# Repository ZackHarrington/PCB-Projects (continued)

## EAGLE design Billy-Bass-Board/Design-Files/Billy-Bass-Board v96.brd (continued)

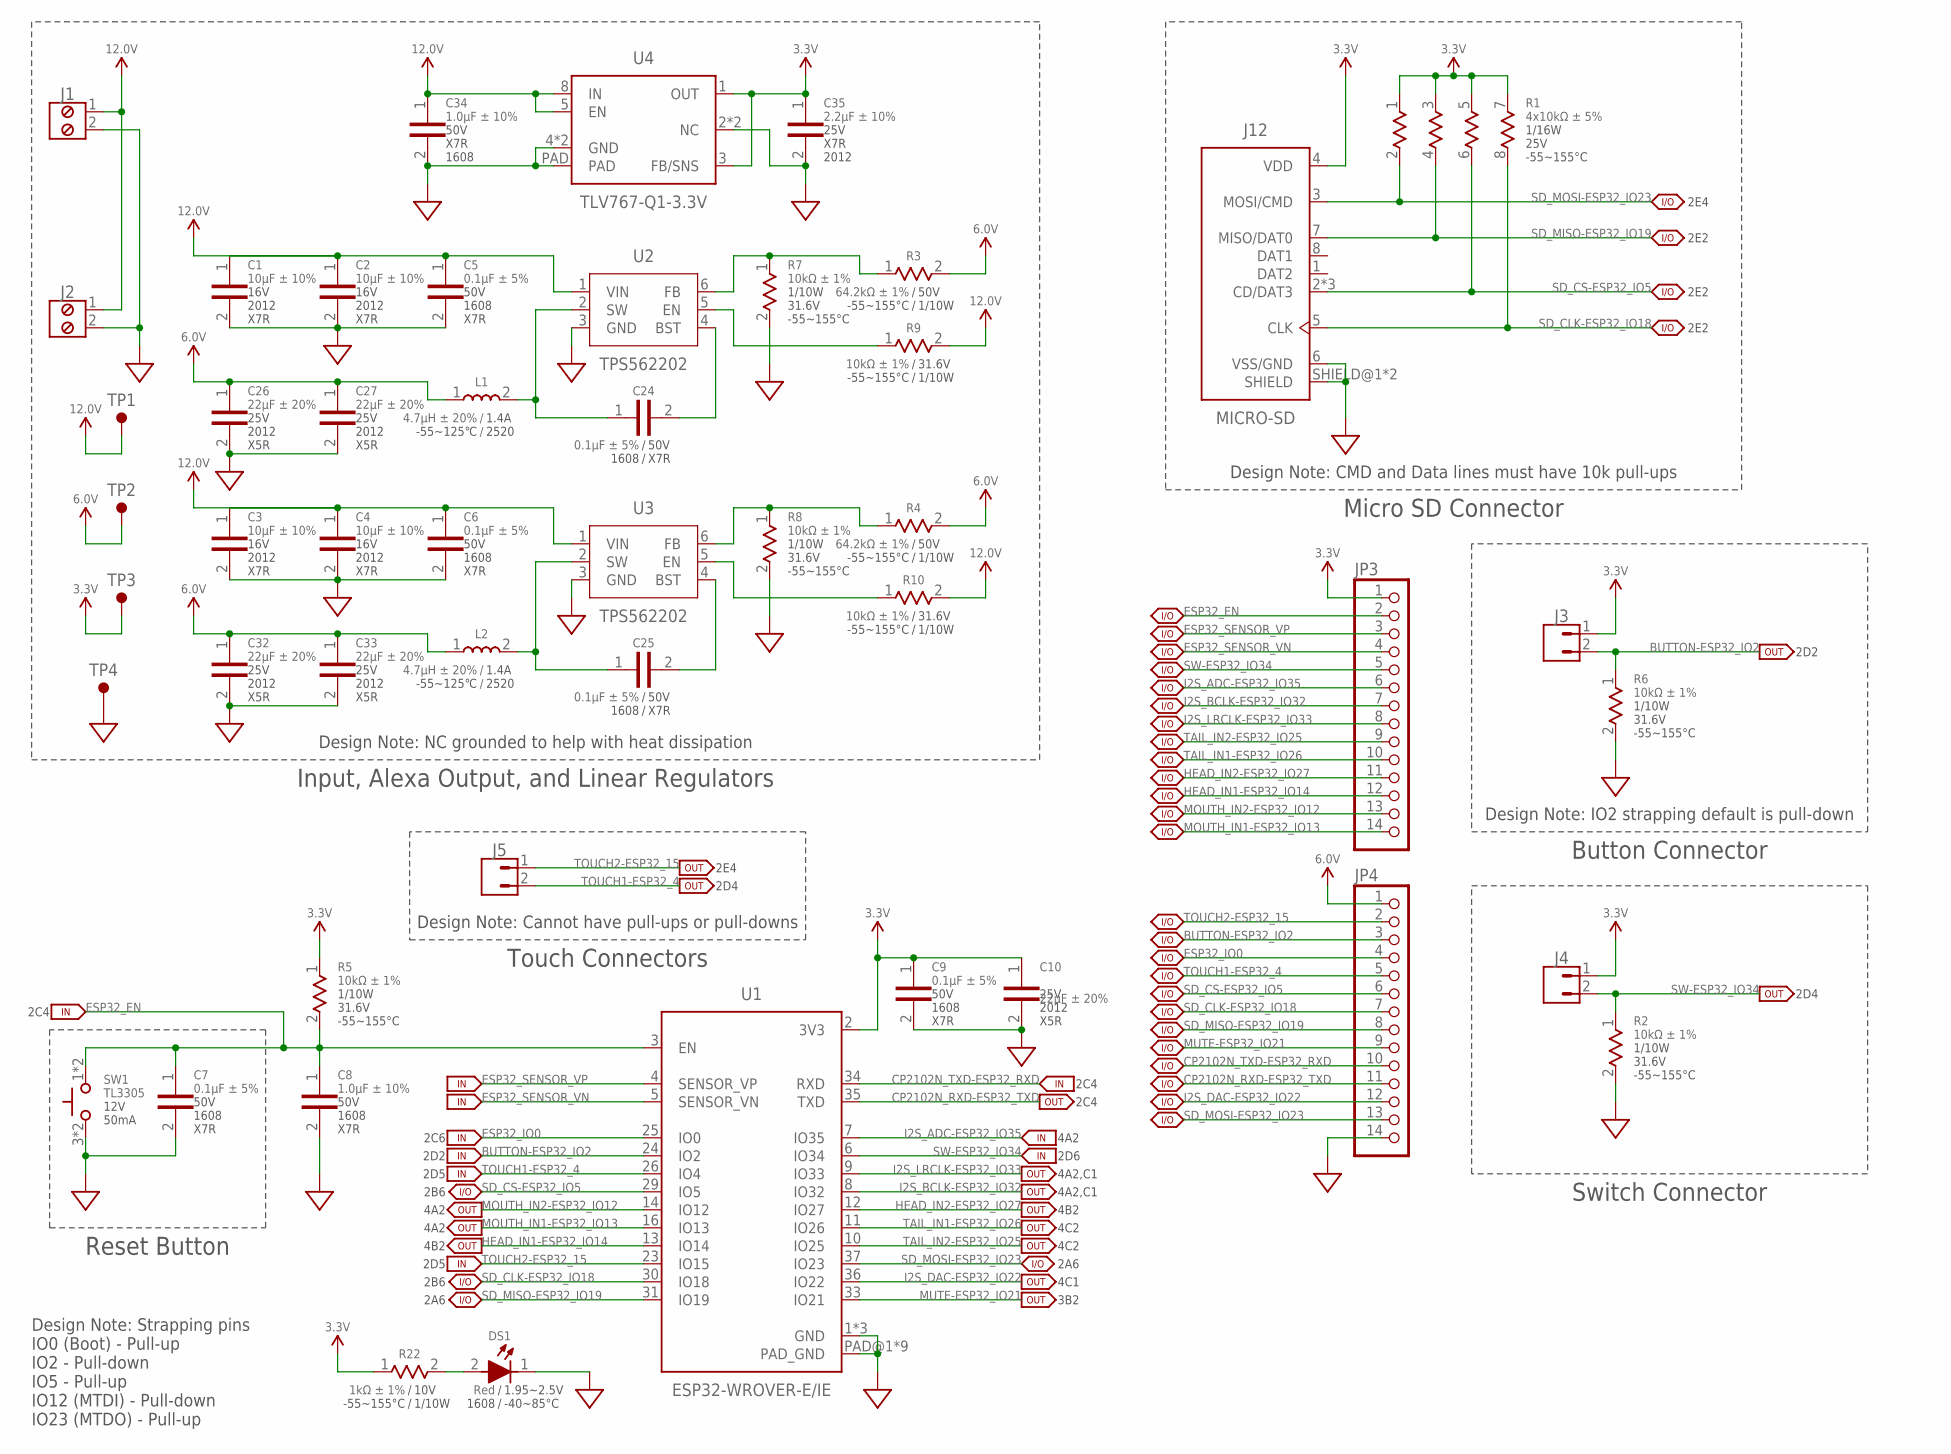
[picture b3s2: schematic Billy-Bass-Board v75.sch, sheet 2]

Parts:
C1, C2, C3, C4: 10µF ± 10%; 2012-SEM
C5, C6, C7, C9, C24, C25: 0.1µF ± 5%; 1608-SEM
C8, C34: 1.0µF ± 10%; 1608-SEM
C10, C26, C27, C32, C33: 22µF ± 20%; 2012-SEM
C35: 2.2µF ± 10%; 2012-SEM
DS1: Red; 1608
J1, J2: MPT-2-SCREW; MPT-0.5/2-2.54
J3, J4, J5: JST-XH-2; B2B-XH-A
J12: MICRO-SD; MEM2061
JP3, JP4: PINHD-1X14; 1X14
L1, L2: 4.7µH ± 20%; 2520-SEM
R1: 4x10kΩ ± 5%; 2010-4P-SEM
R2, R5, R6, R7, R8, R9, R10: 10kΩ ± 1%; 1608-SEM
R3, R4: 64.2kΩ ± 1%; 1608-SEM
R22: 1kΩ ± 1%; 1608-SEM
SW1: TL3305
TP1, TP2, TP3, TP4: TEST-POINT
U1: ESP32-WROVER-E/IE
U2, U3: TPS562202; SOT563
U4: TLV767-Q1-3.3V; VSON

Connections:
3.3V: C9.1, C10.1, C35.1, J3.1, J4.1, J12.4 (VDD), JP3.1, R1.1, R1.3, R1.5, R1.7, R5.1, R22.1, TP3.TP, U1.2 (3V3), U4.1 (OUT), U4.3 (FB/SNS); also elsewhere on the board
6.0V: C26.1, C27.1, C32.1, C33.1, JP4.1, L1.1, L2.1, R3.2, R4.2, TP2.TP; also elsewhere on the board
12.0V: C1.1, C2.1, C3.1, C4.1, C5.1, C6.1, C34.1, J1.1, J2.1, R9.2, R10.2, TP1.TP, U2.1 (VIN), U3.1 (VIN), U4.5 (EN), U4.8 (IN)
BUTTON-ESP32_IO2: J3.2, JP4.3, R6.1, U1.24 (IO2)
CP2102N_RXD-ESP32_TXD: JP4.11, U1.35 (TXD)
CP2102N_TXD-ESP32_RXD: JP4.10, U1.34 (RXD)
ESP32_EN: C7.1, C8.1, JP3.2, R5.2, SW1.1 (2), SW1.2, U1.3 (EN)
ESP32_IO0: JP4.4, U1.25 (IO0)
ESP32_SENSOR_VN: JP3.4, U1.5 (SENSOR_VN)
ESP32_SENSOR_VP: JP3.3, U1.4 (SENSOR_VP)
GND: C1.2, C2.2, C3.2, C4.2, C5.2, C6.2, C7.2, C8.2, C9.2, C10.2, C26.2, C27.2, C32.2, C33.2, C34.2, C35.2, DS1.1, J1.2, J2.2, J12.6 (VSS/GND), J12.SHIELD@1 (SHIELD), J12.SHIELD@2 (SHIELD), JP4.14, R2.2, R6.2, R7.2, R8.2, SW1.3 (1), SW1.4 (1), TP4.TP, U1.1 (GND), U1.15 (GND), U1.38 (GND), U1.PAD@1 (PAD_GND), U1.PAD@2 (PAD_GND), U1.PAD@3 (PAD_GND), U1.PAD@4 (PAD_GND), U1.PAD@5 (PAD_GND), U1.PAD@6 (PAD_GND), U1.PAD@7 (PAD_GND), U1.PAD@8 (PAD_GND), U1.PAD@9 (PAD_GND), U2.3 (GND), U3.3 (GND), U4.2 (NC), U4.4 (GND), U4.6 (GND), U4.7 (NC), U4.PAD; also elsewhere on the board
HEAD_IN1-ESP32_IO14: JP3.12, U1.13 (IO14); also elsewhere on the board
HEAD_IN2-ESP32_IO27: JP3.11, U1.12 (IO27); also elsewhere on the board
I2S_ADC-ESP32_IO35: JP3.6, U1.7 (IO35); also elsewhere on the board
I2S_BCLK-ESP32_IO32: JP3.7, U1.8 (IO32); also elsewhere on the board
I2S_DAC-ESP32_IO22: JP4.12, U1.36 (IO22); also elsewhere on the board
I2S_LRCLK-ESP32_IO33: JP3.8, U1.9 (IO33); also elsewhere on the board
MOUTH_IN1-ESP32_IO13: JP3.14, U1.16 (IO13); also elsewhere on the board
MOUTH_IN2-ESP32_IO12: JP3.13, U1.14 (IO12); also elsewhere on the board
MUTE-ESP32_IO21: JP4.9, U1.33 (IO21); also elsewhere on the board
unnamed: DS1.2, R22.2
SD_CLK-ESP32_IO18: J12.5 (CLK), JP4.7, R1.8, U1.30 (IO18)
SD_CS-ESP32_IO5: J12.2 (CD/DAT3), J12.CD@1 (CD/DAT3), J12.CD@2 (CD/DAT3), JP4.6, R1.6, U1.29 (IO5)
SD_MISO-ESP32_IO19: J12.7 (MISO/DAT0), JP4.8, R1.4, U1.31 (IO19)
SD_MOSI-ESP32_IO23: J12.3 (MOSI/CMD), JP4.13, R1.2, U1.37 (IO23)
SW-ESP32_IO34: J4.2, JP3.5, R2.1, U1.6 (IO34)
TAIL_IN1-ESP32_IO26: JP3.10, U1.11 (IO26); also elsewhere on the board
TAIL_IN2-ESP32_IO25: JP3.9, U1.10 (IO25); also elsewhere on the board
TOUCH1-ESP32_4: J5.2, JP4.5, U1.26 (IO4)
TOUCH2-ESP32_15: J5.1, JP4.2, U1.23 (IO15)
TPS5622021_BST: C24.2, U2.4 (BST)
TPS5622021_EN: R9.1, U2.5 (EN)
TPS5622021_FB: R3.1, R7.1, U2.6 (FB)
TPS5622021_SW: C24.1, L1.2, U2.2 (SW)
TPS5622022_BST: C25.2, U3.4 (BST)
TPS5622022_EN: R10.1, U3.5 (EN)
TPS5622022_FB: R4.1, R8.1, U3.6 (FB)
TPS5622022_SW: C25.1, L2.2, U3.2 (SW)

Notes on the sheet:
Input, Alexa Output, and Linear Regulators
Reset Button
2E4
2E2
Micro SD Connector
2D2
Button Connector
Design Note: IO2 strapping default is pull-down
2C4
2A6
2C6
2B6
Design Note: NC grounded to help with heat dissipation
Design Note: CMD and Data lines must have 10k pull-ups
Design Note: Strapping pins IO0 (Boot) - Pull-up IO2 - Pull-down IO5 - Pull-up IO12 (MTDI) - Pull-down IO23 (MTDO) - Pull-up
Design Note: Cannot have pull-ups or pull-downs
Touch Connectors
Switch Connector
4A2
4B2
4C2
2D4
2D5
2D6
4A2,C1
4C1
3B2

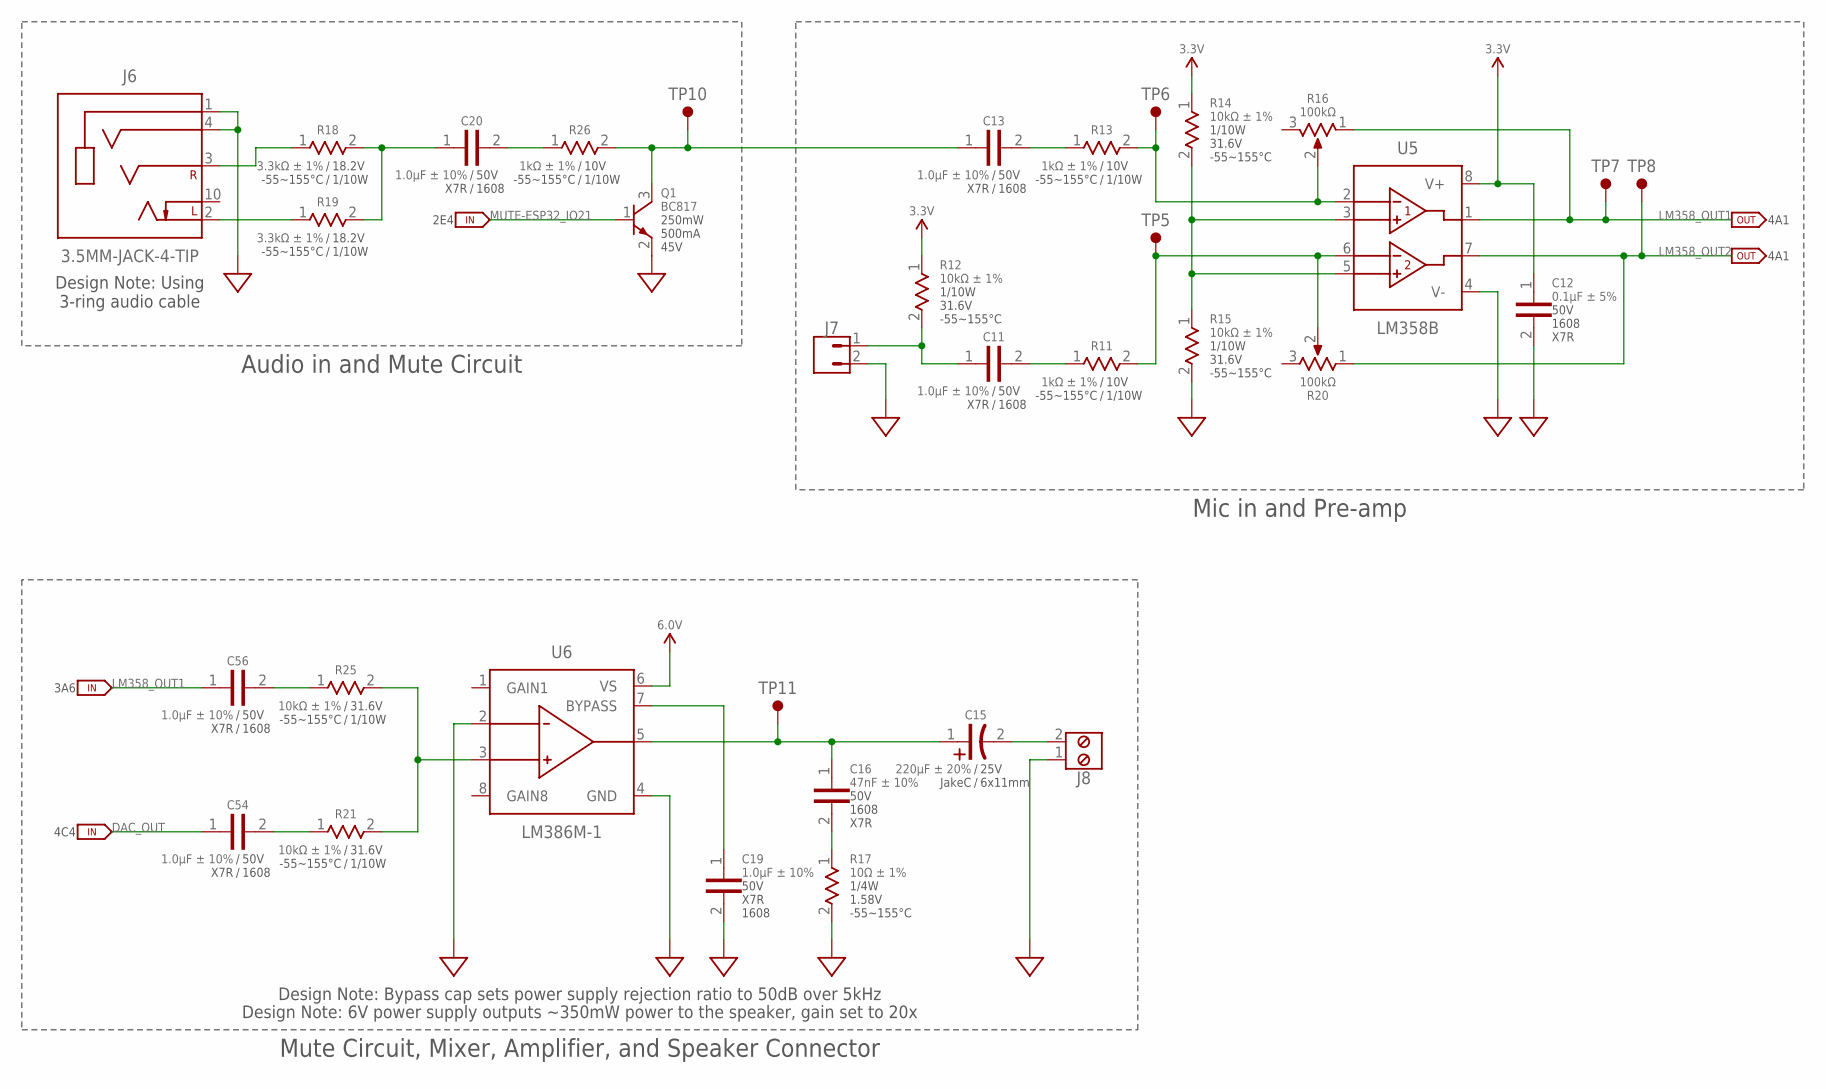
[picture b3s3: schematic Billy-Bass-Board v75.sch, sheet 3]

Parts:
C11, C13, C19, C20, C54, C56: 1.0µF ± 10%; 1608-SEM
C12: 0.1µF ± 5%; 1608-SEM
C15: 220µF ± 20%; 6X11-E-FLAT-REV
C16: 47nF ± 10%; 1608-SEM
J6: 3.5MM-JACK-4-TIP; SJ2-358940-SMT
J7: JST-XH-2; B2B-XH-A
J8: MPT-2-SCREW; MPT-0.5/2-2.54
Q1: BC817; SOT-23-3
R11, R13, R26: 1kΩ ± 1%; 1608-SEM
R12, R14, R15, R21, R25: 10kΩ ± 1%; 1608-SEM
R16, R20: 100kΩ; 3314J
R17: 10Ω ± 1%; 3216-SEM
R18, R19: 3.3kΩ ± 1%; 1608-SEM
TP5, TP6, TP7, TP8, TP10, TP11: TEST-POINT
U5: LM358B; D0008A-SOIC
U6: LM386M-1; D0008A-SOIC

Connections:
3.3V: C12.1, R12.1, R14.1, U5.8 (V+); also elsewhere on the board
6.0V: U6.6 (VS); also elsewhere on the board
AUX_LEFT: J6.2 (TIP), R19.1
AUX_MIXED: C20.1, R18.2, R19.2
AUX_MUTE: C13.1, Q1.3 (C), R26.2, TP10.TP
AUX_RIGHT: J6.3 (RING_1), R18.1
DAC_OUT: C54.1; also elsewhere on the board
GND: C12.2, C19.2, J6.1 (SLEEVE), J6.4 (RING_2), J7.2, J8.1, Q1.2 (E), R15.2, R17.2, U5.4 (V-), U6.2 (-INPUT), U6.4 (GND); also elsewhere on the board
LM358_IN1-: R13.2, R16.2, TP6.TP, U5.2 (IN1-)
LM358_IN2-: R11.2, R20.2, TP5.TP, U5.6 (IN2-)
LM358_IN+: R14.2, R15.1, U5.3 (IN1+), U5.5 (IN2+)
LM358_OUT1: C56.1, R16.1, TP7.TP, U5.1 (OUT1); also elsewhere on the board
LM358_OUT2: R20.1, TP8.TP, U5.7 (OUT2); also elsewhere on the board
LM386M_BYPASS: C19.1, U6.7 (BYPASS)
LM386M_IN+: R21.2, R25.2, U6.3 (+INPUT)
LM386M_OUT: C15.1, C16.1, TP11.TP, U6.5 (VOUT)
MIC+: C11.1, J7.1, R12.2
MUTE-ESP32_IO21: Q1.1 (B); also elsewhere on the board
unnamed: C54.2, R21.1
unnamed: C13.2, R13.1
unnamed: C20.2, R26.1
unnamed: C56.2, R25.1
unnamed: C11.2, R11.1
unnamed: C16.2, R17.1
SPEAKER+: C15.2, J8.2

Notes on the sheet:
Design Note: Using 3-ring audio cable
Mic in and Pre-amp
Mute Circuit, Mixer, Amplifier, and Speaker Connector
Design Note: 6V power supply outputs ~350mW power to the speaker, gain set to 20x
4A1
Design Note: Bypass cap sets power supply rejection ratio to 50dB over 5kHz
Audio in and Mute Circuit
2E4
4C4
3A6

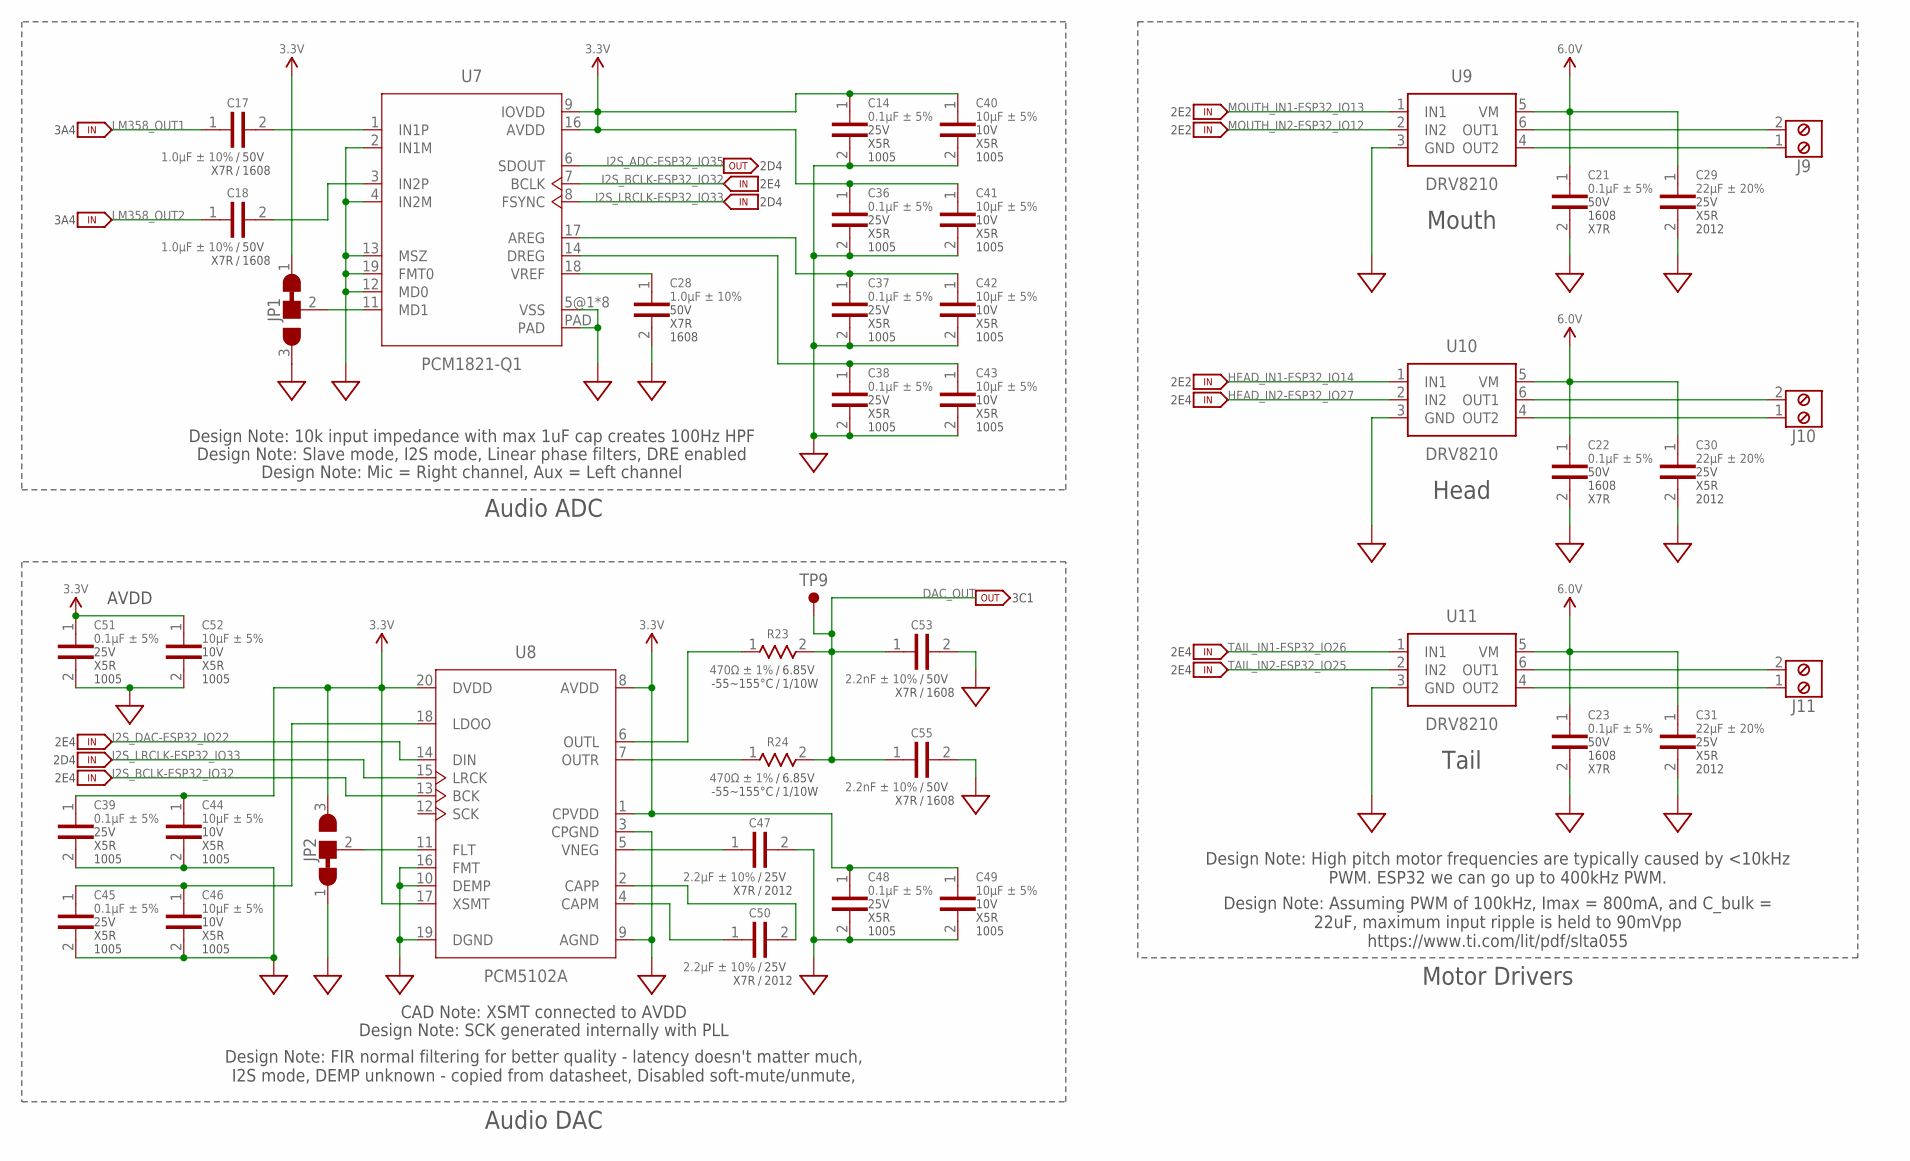
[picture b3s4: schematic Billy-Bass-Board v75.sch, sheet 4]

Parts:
C14, C36, C37, C38, C39, C45, C48, C51: 0.1µF ± 5%; 1005-SEM
C17, C18, C28: 1.0µF ± 10%; 1608-SEM
C21, C22, C23: 0.1µF ± 5%; 1608-SEM
C29, C30, C31: 22µF ± 20%; 2012-SEM
C40, C41, C42, C43, C44, C46, C49, C52: 10µF ± 5%; 1005-SEM
C47, C50: 2.2µF ± 10%; 2012-SEM
C53, C55: 2.2nF ± 10%; 1608-SEM
J9, J10, J11: MPT-2-SCREW; MPT-0.5/2-2.54
JP1, JP2: JUMPER-2-BRIDGED-1; JUMPER-PAD-2-BRIDGED-1
R23, R24: 470Ω ± 1%; 1608-SEM
TP9: TEST-POINT
U7: PCM1821-Q1; WQFN
U8: PCM5102A; TSSOP-20
U9, U10, U11: DRV8210; SOT563

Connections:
3.3V: C14.1, C36.1, C39.1, C40.1, C41.1, C44.1, C48.1, C49.1, C51.1, C52.1, JP1.1, JP2.3, U7.9 (IOVDD), U7.16 (AVDD), U8.1 (CPVDD), U8.8 (AVDD), U8.17 (XSMT), U8.20 (DVDD); also elsewhere on the board
6.0V: C21.1, C22.1, C23.1, C29.1, C30.1, C31.1, U9.5 (VM), U10.5 (VM), U11.5 (VM); also elsewhere on the board
DAC_OUT: C53.1, C55.1, R23.2, R24.2, TP9.TP; also elsewhere on the board
DRV82101_OUT1: J9.2, U9.6 (OUT1)
DRV82101_OUT2: J9.1, U9.4 (OUT2)
DRV82102_OUT1: J10.2, U10.6 (OUT1)
DRV82102_OUT2: J10.1, U10.4 (OUT2)
DRV82103_OUT1: J11.2, U11.6 (OUT1)
DRV82103_OUT2: J11.1, U11.4 (OUT2)
GND: C14.2, C21.2, C22.2, C23.2, C28.2, C29.2, C30.2, C31.2, C36.2, C37.2, C38.2, C39.2, C40.2, C41.2, C42.2, C43.2, C44.2, C45.2, C46.2, C47.2, C48.2, C49.2, C51.2, C52.2, C53.2, C55.2, JP1.3, JP2.1, U7.2 (IN1M), U7.4 (IN2M), U7.5@1 (VSS), U7.5@2 (VSS), U7.10@1 (VSS), U7.10@2 (VSS), U7.12 (MD0), U7.13 (MSZ), U7.15@1 (VSS), U7.15@2 (VSS), U7.19 (FMT0), U7.20@1 (VSS), U7.20@2 (VSS), U7.PAD, U8.3 (CPGND), U8.9 (AGND), U8.10 (DEMP), U8.16 (FMT), U8.19 (DGND), U9.3 (GND), U10.3 (GND), U11.3 (GND); also elsewhere on the board
HEAD_IN1-ESP32_IO14: U10.1 (IN1); also elsewhere on the board
HEAD_IN2-ESP32_IO27: U10.2 (IN2); also elsewhere on the board
I2S_ADC-ESP32_IO35: U7.6 (SDOUT); also elsewhere on the board
I2S_BCLK-ESP32_IO32: U7.7 (BCLK), U8.13 (BCK); also elsewhere on the board
I2S_DAC-ESP32_IO22: U8.14 (DIN); also elsewhere on the board
I2S_LRCLK-ESP32_IO33: U7.8 (FSYNC), U8.15 (LRCK); also elsewhere on the board
LM358_OUT1: C17.1; also elsewhere on the board
LM358_OUT2: C18.1; also elsewhere on the board
MOUTH_IN1-ESP32_IO13: U9.1 (IN1); also elsewhere on the board
MOUTH_IN2-ESP32_IO12: U9.2 (IN2); also elsewhere on the board
unnamed: JP1.2, U7.11 (MD1)
PCM1821_AREG: C37.1, C42.1, U7.17 (AREG)
PCM1821_DREG: C38.1, C43.1, U7.14 (DREG)
PCM1821_IN1P: C17.2, U7.1 (IN1P)
PCM1821_IN2P: C18.2, U7.3 (IN2P)
PCM1821_VREF: C28.1, U7.18 (VREF)
PCM5102A_CAPM: C50.1, U8.4 (CAPM)
PCM5102A_CAPP: C50.2, U8.2 (CAPP)
PCM5102A_FLT: JP2.2, U8.11 (FLT)
PCM5102A_LDOO: C45.1, C46.1, U8.18 (LDOO)
PCM5102A_OUTL: R23.1, U8.6 (OUTL)
PCM5102A_OUTR: R24.1, U8.7 (OUTR)
PCM5102A_VNEG: C47.1, U8.5 (VNEG)
TAIL_IN1-ESP32_IO26: U11.1 (IN1); also elsewhere on the board
TAIL_IN2-ESP32_IO25: U11.2 (IN2); also elsewhere on the board

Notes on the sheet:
Design Note: Assuming PWM of 100kHz, Imax = 800mA, and C_bulk = 22uF, maximum input ripple is held to 90mVpp https://www.ti.com/lit/pdf/slta055
Mouth
Head
Tail
2E2
2E4
Audio ADC
Design Note: Mic = Right channel, Aux = Left channel
Design Note: Slave mode, I2S mode, Linear phase filters, DRE enabled
Design Note: 10k input impedance with max 1uF cap creates 100Hz HPF
2D4
Motor Drivers
3A4
Design Note: High pitch motor frequencies are typically caused by <10kHz PWM. ESP32 we can go up to 400kHz PWM.
CAD Note: XSMT connected to AVDD
Design Note: FIR normal filtering for better quality - latency doesn't matter much, I2S mode, DEMP unknown - copied from datasheet, Disabled soft-mute/unmute,
Design Note: SCK generated internally with PLL
AVDD
Audio DAC
3C1

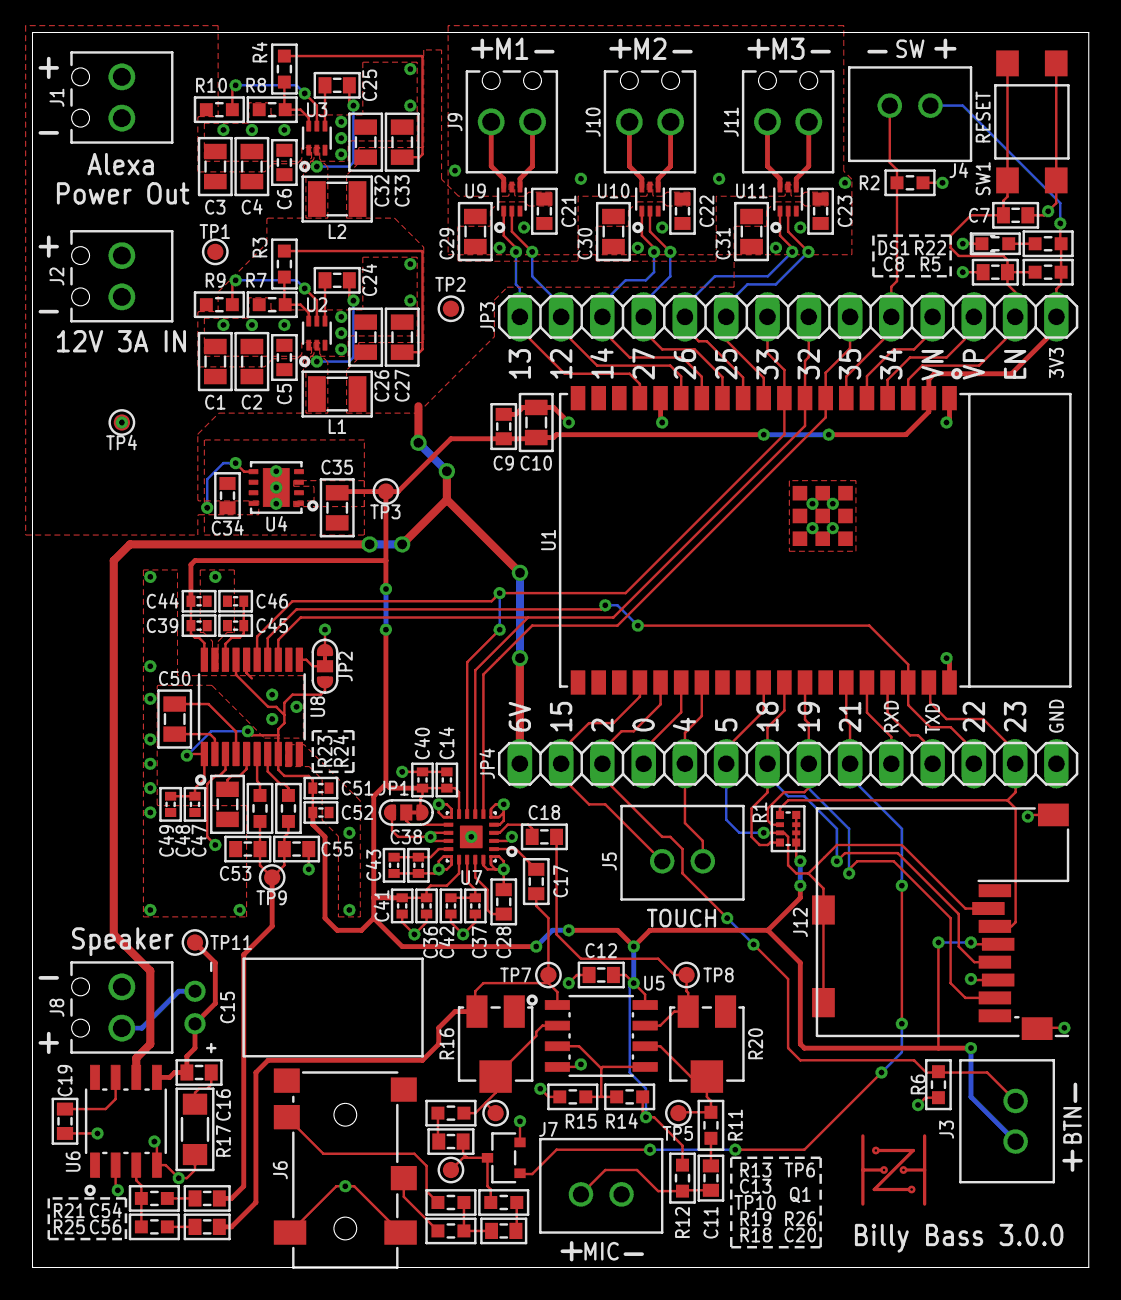
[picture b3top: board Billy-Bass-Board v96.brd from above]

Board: 2 copper layers, 65.0 x 76.0 mm, 126 parts (0 on the bottom side), 78 nets.

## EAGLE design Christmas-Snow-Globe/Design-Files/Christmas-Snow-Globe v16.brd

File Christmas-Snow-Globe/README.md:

# Christmas Snow Globe 

In this project, I combined my hobbies of PCB and electronics design, 3D modeling, 3D printing, and programming to create personalized snow globes for the holiday season. This README goes through the stages of development for this project and showcases the final build at the end.

## Introduction

I try to create personalized gifts for the holidays, and this year I set out to build something using lights and custom PCBs. After a brainstorming session with my roommate, I decided it would be really neat to incorporate personalized Lego minifigures of everyone. The only way of doing this that came to mind was building a snow globe around them. After plugging my thoughts into the Bing Image Generator and coming up with some concept drawings, I settled on keeping it simple with some timer-controlled LEDs and 3D printed casing. This way I could create a simple yet elegant design, while most importantly, having time to finish it. 

## Features

I initially decided on some key features for the snow globes, and then designed around them. These included:
- Custom Lego minifigures of each person or couple - which I ordered from pick-a-brick
- LED fairy lights to illuminate the minifigures and fit the holiday theme
- A 6-hour ON, 18-hour OFF timer for ease of use
- Battery powered - for ease of use and as a low power consumption challenge

## Design

After ordering the minifigure parts, I also ordered some cheap snow globe tops that would fit. For this I chose 2.7in (69mm) because everything else felt too big. The first part of the design entailed deciding on what batteries and electrical components to use, along with how they would all fit into the snow globe. Next, once I had a general PCB layout and model from Fusion360, I loaded it into Blender and created the snow globe stand parts. Lastly, I designed the fake snow the minifigures would stand on by modeling Lego piece connectors.

### 1. Electronic Design

The first challenge for the electronics design was how to build a precise 6-hour timer. I went through a few concepts such as a crystal oscillator and counter circuit but ultimately settled on using the cheap 8-bit ATtiny85 because it can be programmed with Arduino, is reliable within ~1 minute, and its power-down mode only draws 0.5uA. 

The next challenge was what batteries to use. I wanted them to be easy to find since I wouldn't be the one replacing them every year, but also to last the full month or two the snow globes were used. After considering size requirements and reading through other documentation, I settled on three AAA batteries. This gave me a voltage range of roughly 4.5 - 3.3V over the battery's life, satisfying the 2.6 - 2.7V requirement of the LED fairy lights and providing ample mAh for the expected 0.5 - 3mA draw (depending on the voltage over the LEDs). 

Lastly, I needed to keep the voltage over the LEDs steady for even brightness and low current consumption. During this time, I found a 2.7V linear regulator with very low quiescent current and decided to add a potentiometer in series with the LED fairy lights to allow for adjustable brightness and current consumption post production.

The final stage of the electronics design was to lay everything out on the PCB. To do this I marked out the snow globe dimensions and made sure to put everything in a good location while trying to make sure it was as simple as possible for everyone to access the batteries. The final render of this board can be seen below.

### 2. 3D Design

After I was set on the electronics and confident they would work, I began to create the stand for the snow globe which would also house the PCB and batteries. Because I originally planned on adding some organic detailing to the outside of the stand, I chose to model everything in Blender. I ultimately liked the simple look of the stand itself better, so it probably wasn't necessary, but since I had everything in Blender I decided to also use some of the displacement modifiers to create a snowy scene for the characters to stand on. Below is a render of the final 3D modeled pieces, unfortunately the minifigure textures didn't copy over when I imported them from a past project.

### 3. Programming

The last big challenge of this project, aside from getting everything in time, was to actually program the ATtiny85 to act as a 6-hour timer. This took a while to learn as I had never used interrupts or 8-bit microprocessors before, but ultimately didn't prove to be too difficult. I found configuring the watchdog as an interrupt gave me a pretty steady average of 8.955s per interrupt. This wasn't amazing in terms of accurately measuring 6 hours, but it was the most power efficient way of doing it. And at the end of the day, no one will notice that the timer originally set to turn on at 5:00 p.m. now turns on at 5:04 p.m. a month later.

## Construction

Here I have included some images of the physical construction of each part and the final product.

### Soldered Board

### Stand Top

### Stand Bottom

### Final Product

Update: After almost 2 months the device is still functional. The LED brightness has dimmed a bit, but they still turn on around roughly the same time indicating the timer and power draw calculations were accurate. 

## License

This is just a hobby creation I made as a gift so feel free to do whatever you want with this design if you happened upon it. However, I would recommend reading the considerations below and modifying it or building your own rather than copying it.

## Project Considerations

The following are some things I learned from this project for myself or anyone else to consider when doing something similar.
- I built the stand to screw into the plastic globes which causes the wire connecting the LED strips to the PCB to coil up and sometimes break. In the future, not screwing in the globes or allowing the PCB itself to rotate may be more reliable.
- The Lego pick-a-brick items took about a month and a half to arrive (I got them 3 days before Christmas) 
- There are more accurate and power conservative ways to create a timer, this was just simple and easy to adjust on the fly
- The AAA batteries worked great but they do slip around on the contacts, they should probably have physical dividers between them to hold them in place.

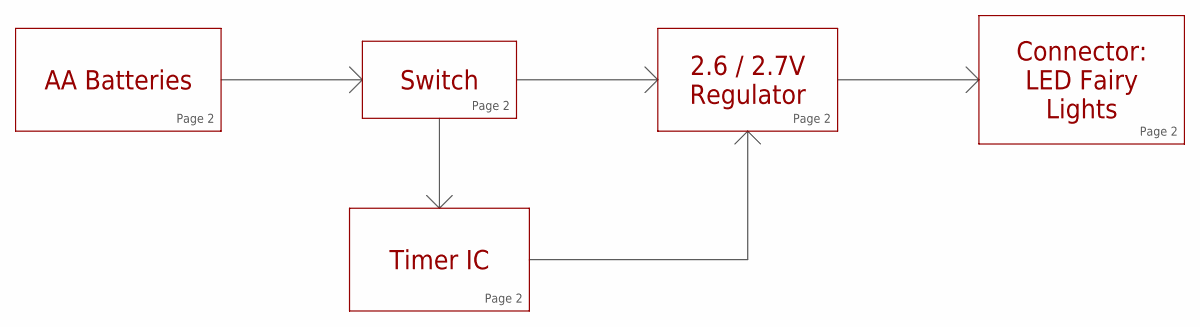
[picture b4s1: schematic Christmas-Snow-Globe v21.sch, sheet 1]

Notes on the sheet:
Switch
AA Batteries
Timer IC
Connector: LED Fairy Lights
2.6 / 2.7V Regulator
Page 2

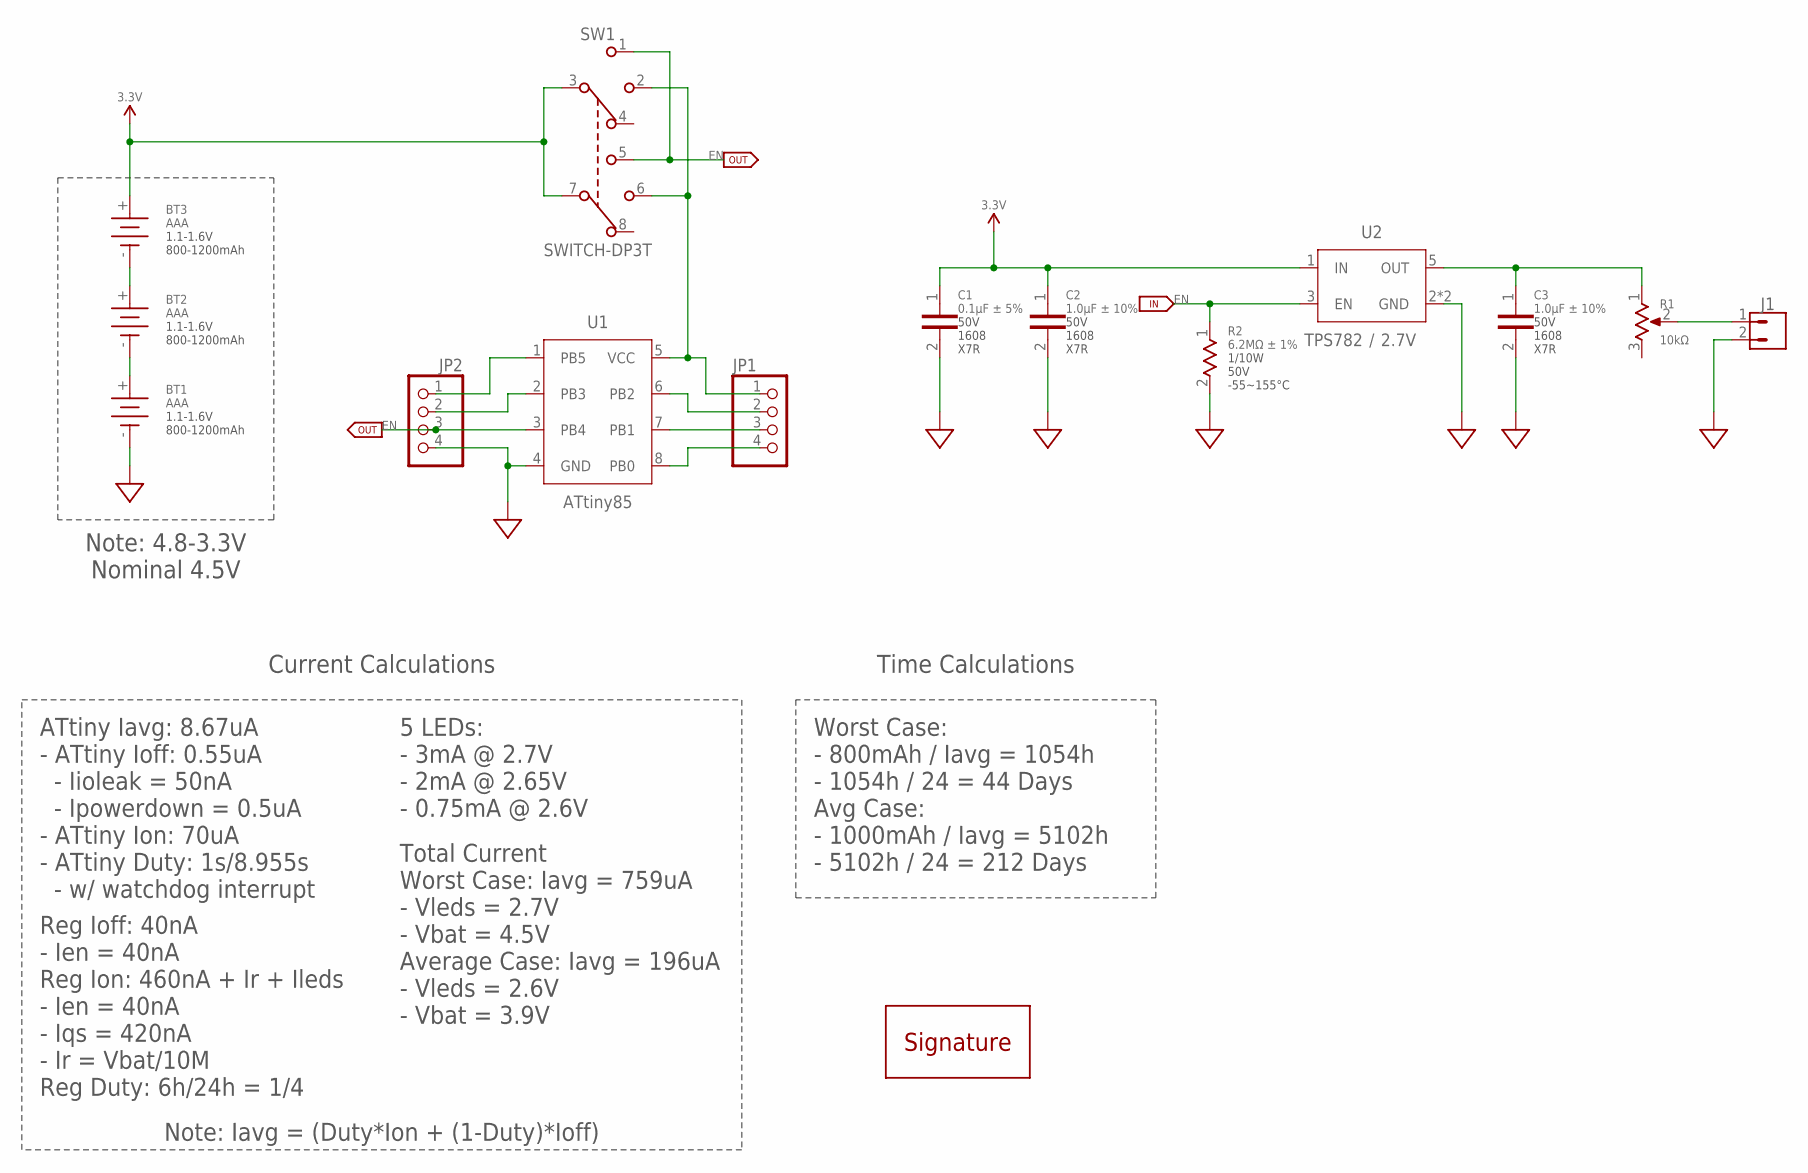
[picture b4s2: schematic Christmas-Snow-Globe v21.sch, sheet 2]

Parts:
BT1, BT2, BT3: AAA; AAA-CONTACTS
C1: 0.1µF ± 5%; 1608-SEM
C2, C3: 1.0µF ± 10%; 1608-SEM
J1: JST-PH-2; B2B-PH-K-S
JP1, JP2: PINHD-1X4; 1X04
R1: 10kΩ; 3314J
R2: 6.2MΩ ± 1%; 1608-SEM
SW1: SWITCH-DP3T; EG2301
U1: ATtiny85; 8P3-PDIP
U2: TPS782; SOT-23-5
U$14: SIGNATURE

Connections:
3.3V: BT3.+, C1.1, C2.1, SW1.3, SW1.7, U2.1 (IN)
EN: JP2.3, R2.1, SW1.1, SW1.5, U1.3 (PB4), U2.3 (EN)
GND: BT1.-, C1.2, C2.2, C3.2, J1.2, JP2.4, R2.2, U1.4 (GND), U2.2 (GND), U2.4 (GND)
LEDS+: J1.1, R1.2
unnamed: BT2.+, BT3.-
unnamed: BT1.+, BT2.-
PB0: JP1.4, U1.8 (PB0)
PB1: JP1.3, U1.7 (PB1)
PB2: JP1.2, U1.6 (PB2)
PB3: JP2.2, U1.2 (PB3)
PB5: JP2.1, U1.1 (PB5)
TIMER: JP1.1, SW1.2, SW1.6, U1.5 (VCC)
TPS782_OUT: C3.1, R1.1, U2.5 (OUT)

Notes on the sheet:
Note: 4.8-3.3V Nominal 4.5V
Current Calculations
ATtiny Iavg: 8.67uA - ATtiny Ioff: 0.55uA - Iioleak = 50nA - Ipowerdown = 0.5uA - ATtiny Ion: 70uA - ATtiny Duty: 1s/8.955s - w/ watchdog interrupt
5 LEDs: - 3mA @ 2.7V - 2mA @ 2.65V - 0.75mA @ 2.6V
Reg Ioff: 40nA - Ien = 40nA Reg Ion: 460nA + Ir + Ileds - Ien = 40nA - Iqs = 420nA - Ir = Vbat/10M Reg Duty: 6h/24h = 1/4
Total Current Worst Case: Iavg = 759uA - Vleds = 2.7V - Vbat = 4.5V Average Case: Iavg = 196uA - Vleds = 2.6V - Vbat = 3.9V
Note: Iavg = (Duty*Ion + (1-Duty)*Ioff)
Time Calculations
Worst Case: - 800mAh / Iavg = 1054h - 1054h / 24 = 44 Days Avg Case: - 1000mAh / Iavg = 5102h - 5102h / 24 = 212 Days

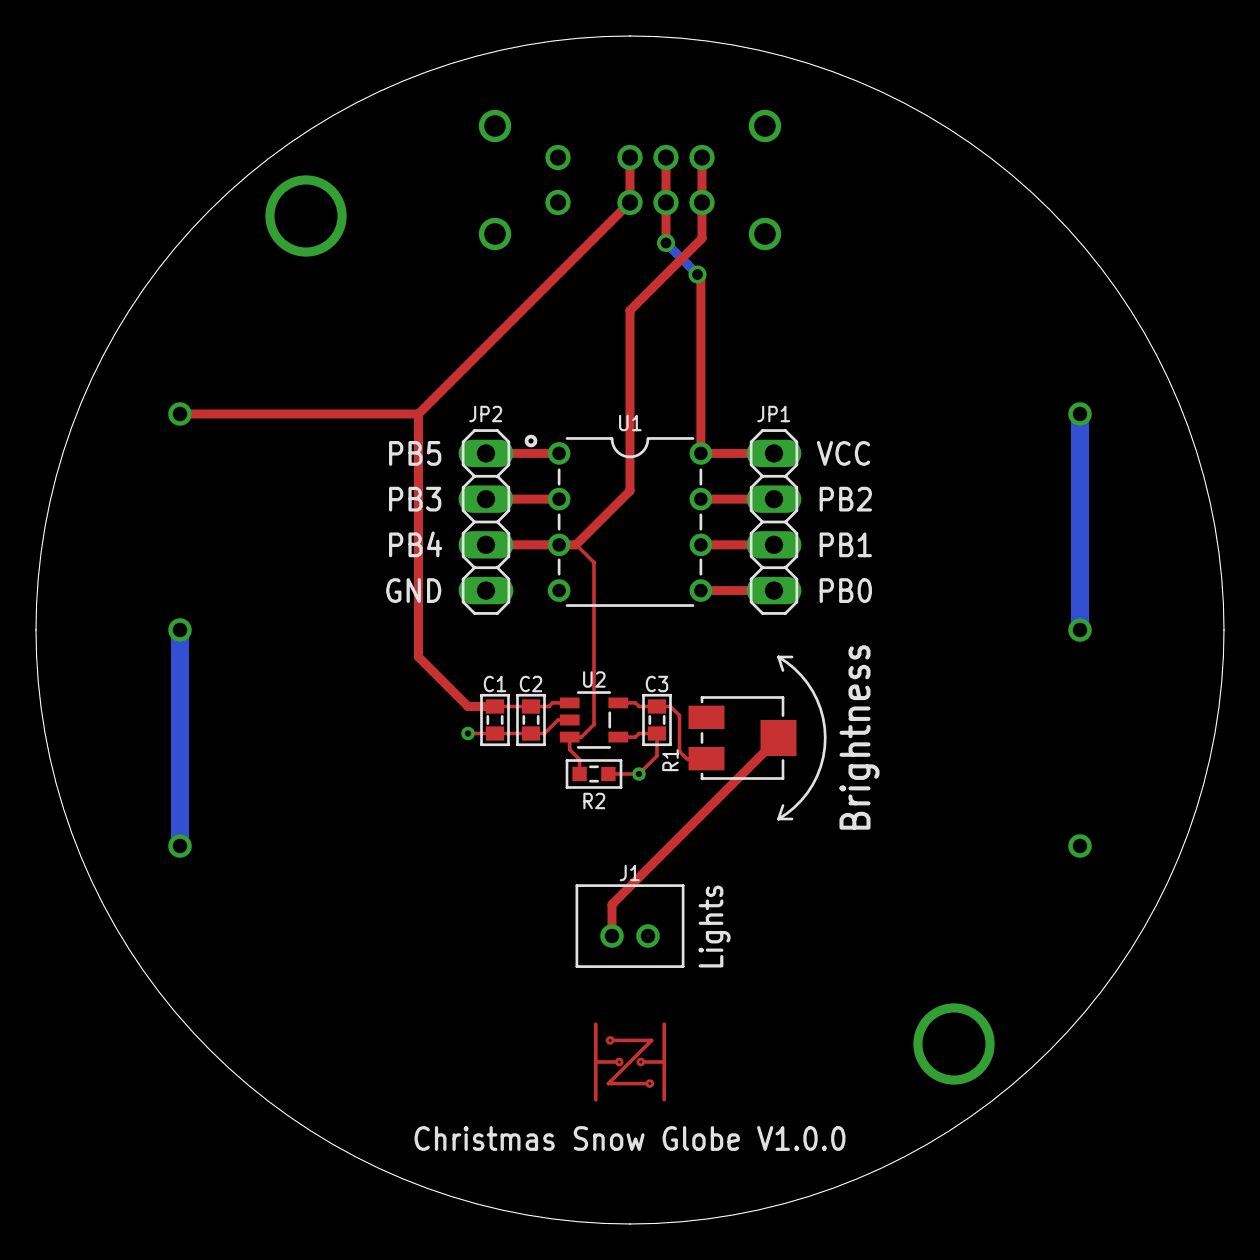
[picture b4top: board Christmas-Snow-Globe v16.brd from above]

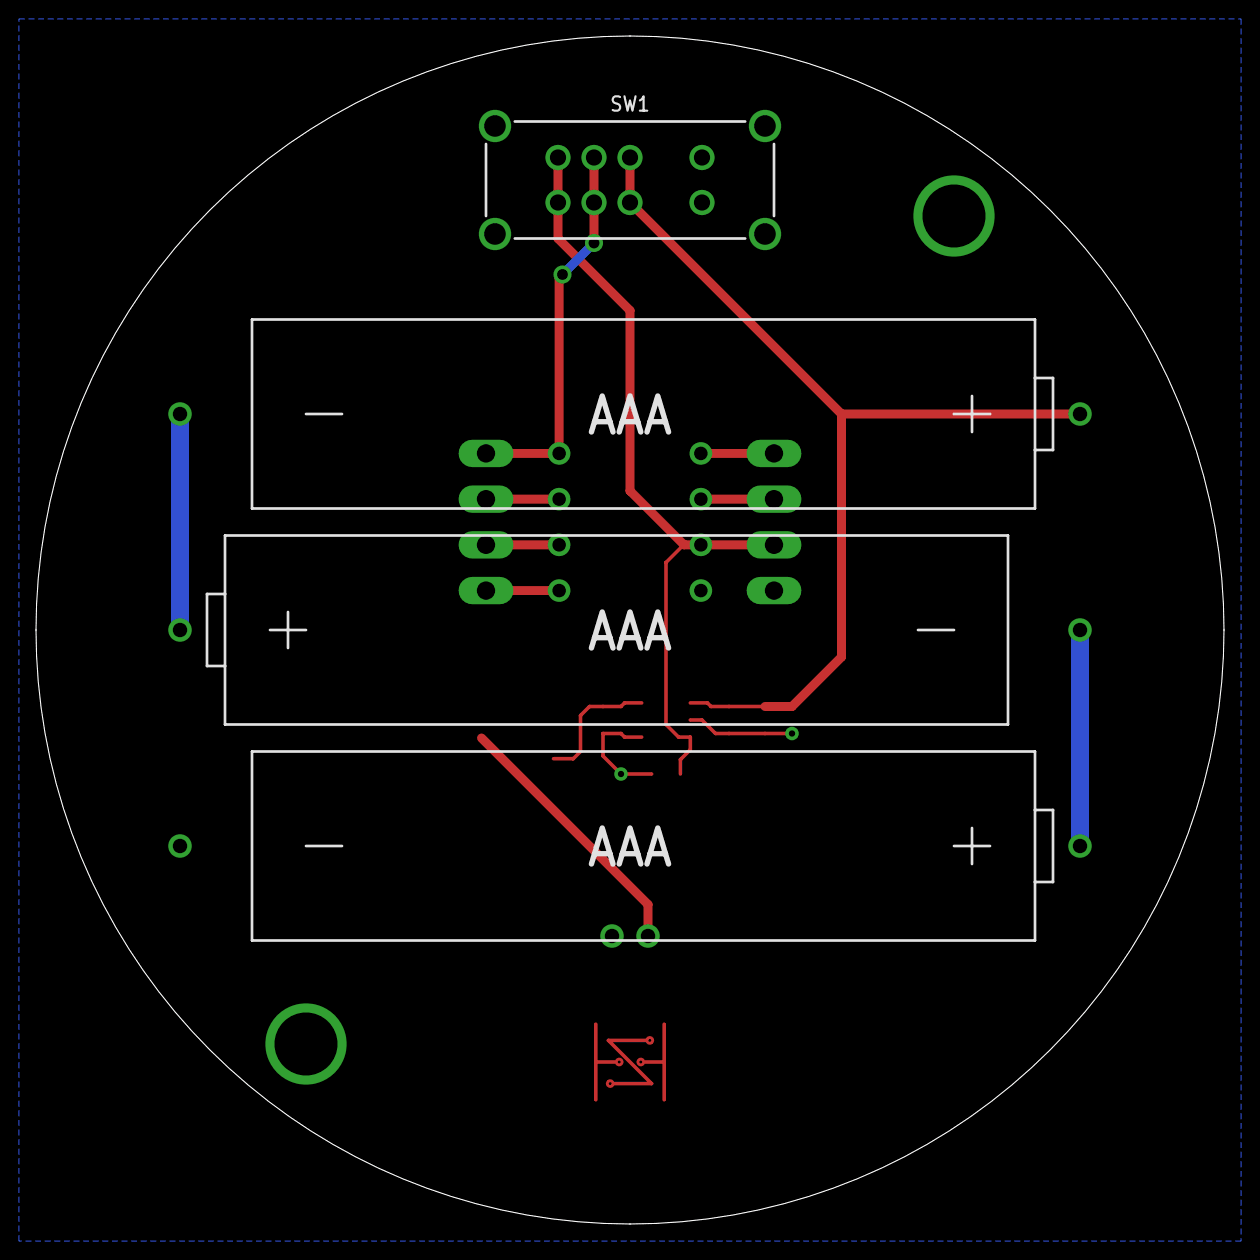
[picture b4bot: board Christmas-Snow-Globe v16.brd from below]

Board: 2 copper layers, 66.0 x 66.0 mm, 15 parts (4 on the bottom side), 13 nets.

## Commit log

2023-04-29 Initial commit with gitignore and README files
2023-04-29 Adding all current project files and libraries
2023-06-04 Updated gitignore for gerber files
2023-06-04 Finished Billy Bass Board V2.0.0
2023-06-10 Updated files to match parts purchased
2024-01-08 Updated gitignore for next large commit
2024-01-09 Few new projects. Migration of all updated projects and libraries to Fusion 360 Elecronics
2024-01-10 Attempted to create a Christmas Snow Globe README
2024-01-10 Adjusted links in Christmas Snow Globe README
2024-01-10 Adjusted links again in Christmas Snow Globe README
2024-01-10 Adjusted links another time in Christmas Snow Globe README
2024-02-18 Added 2 month update
2024-03-21 Updated .gitingnore
2024-03-21 Billy Bass Board v3.0.0 Update
2024-03-22 Updated Billy-Bass-Board README
2024-03-22 Updated Billy-Bass-Board README grammar
2024-10-13 Edited .gitignore for migration to KiCAD
2024-10-13 Migrated libraries to KiCAD and started testing a new chess board project
2024-12-28 Added Greek Keyboard Project
2024-12-28 Adjusted photos
